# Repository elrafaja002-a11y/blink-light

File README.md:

# blink-light
I made this projekt with hackclub togheter. VERY NICE!

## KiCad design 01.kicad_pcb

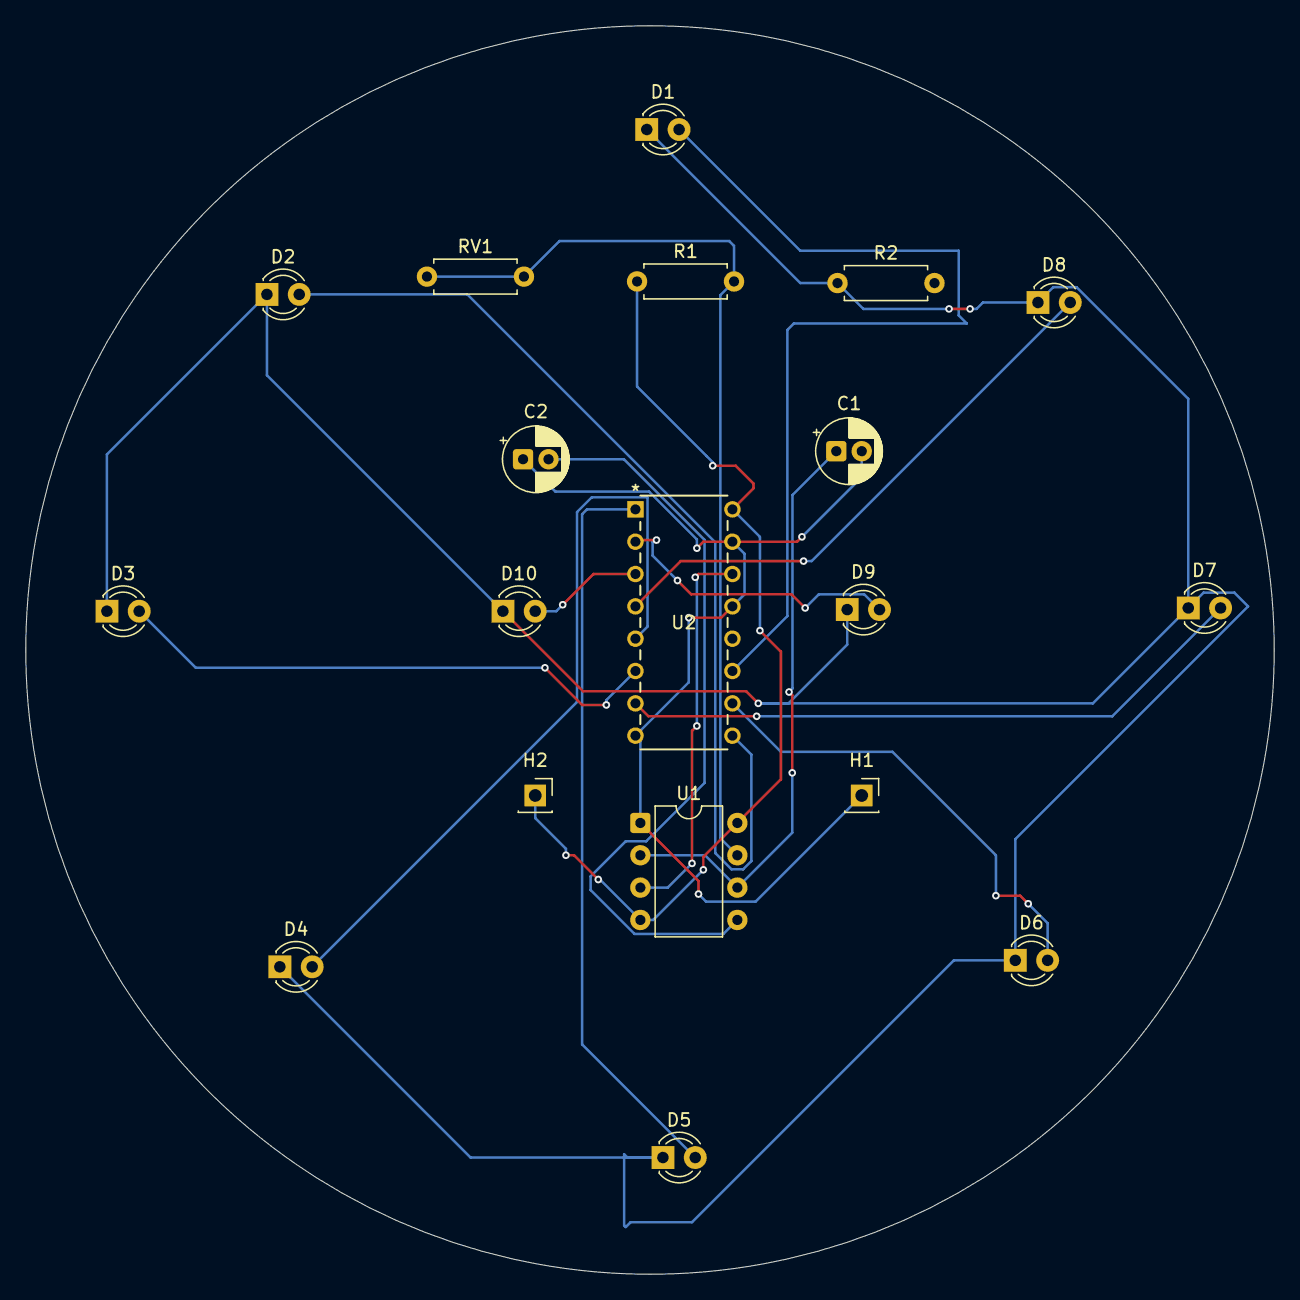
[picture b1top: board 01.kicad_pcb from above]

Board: 2 copper layers, 98.1 x 98.1 mm, 19 parts (0 on the bottom side), 17 nets.

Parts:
C1: C_Polarized; CP_Radial_D5.0mm_P2.00mm
C2: C; CP_Radial_D5.0mm_P2.00mm
D1, D2, D3, D4, D5, D6, D7, D8, D9, D10: LED; LED_D3.0mm
H1, H2: MountingHole_Pad; PinSocket_1x01_P2.54mm_Vertical
R1: 1000; R_Axial_DIN0207_L6.3mm_D2.5mm_P7.62mm_Horizontal
R2: 470; R_Axial_DIN0207_L6.3mm_D2.5mm_P7.62mm_Horizontal
RV1: R_Potentiometer; R_Axial_DIN0207_L6.3mm_D2.5mm_P7.62mm_Horizontal
U1: NE555P; DIP-8_W7.62mm
U2: 4017; N16

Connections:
+5V: H2.1, R1.1, U1.4 (~RST), U1.8 (VCC), U2.16 (VDD)
GND: C1.2, C2.1, H1.1, U1.1 (GND), U2.8 (VSS), U2.13 (CKEN), U2.15 (Reset)
unnamed: D1.2 (A), U2.11 (Q9)
unnamed: D1.1 (K), D2.1 (K), D3.1 (K), D4.1 (K), D5.1 (K), D6.1 (K), D7.1 (K), D8.1 (K), D9.1 (K), D10.1 (K), R2.1
unnamed: D2.2 (A), U2.9 (Q8)
unnamed: D3.2 (A), U2.6 (Q7)
unnamed: D4.2 (A), U2.5 (Q6)
unnamed: D5.2 (A), U2.1 (Q5)
unnamed: D6.2 (A), U2.10 (Q4)
unnamed: D7.2 (A), U2.7 (Q3)
unnamed: D8.2 (A), U2.4 (Q2)
unnamed: D9.2 (A), U2.2 (Q1)
unnamed: D10.2 (A), U2.3 (Q0)
unnamed: C2.2, U1.5 (CONT)
unnamed: R1.2, RV1.1, RV1.2, U1.7 (DISCH)
OUT: U1.3 (OUT), U2.14 (CLK)
TR: C1.1, U1.2 (TRIG), U1.6 (THRES)
